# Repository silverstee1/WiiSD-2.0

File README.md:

# WiiSD-2.0
WiiSD 2.0 Upgrade PCB

Replacement upgrade PCB for WiiSD adapters sold on aliexpress/amazon etc to V2.0 for use on GameCube's Front Memcard Slot B

Based on the SD2SP2 2.0 made by Extrems, Thank you for your hard work!

**Important**

When using the adapter make sure to have the Latest Version of Swiss, Due to the way Swiss handles it in SLOT A it 
acts like a normal speed Passive SDGecko, in SLOT B it works in Semi-Passive 2.0 enhanced speed mode.

https://github.com/emukidid/swiss-gc

WiiSD 2.0 BOM
=====================================
The PCB must be ordered (e.g. from jlcpcb) in 0.8mm thickness with surface finish ENIG at minimum.

**WiiSD V2.0 PCB**

**J2:** SD Slot - Digikey Part# 2223-SD-4-BCT-ND

LCSC Part# C7529393

alt LCSC Part# C266601 , C961674

**U1:** OR Gate IC - DigiKey Part# 296-1093-1-ND

LCSC Part# C7470

Alt Nexperia Digikey Part# 1727-3067-1-ND

LCSC Alt Nexperia Part# C12488

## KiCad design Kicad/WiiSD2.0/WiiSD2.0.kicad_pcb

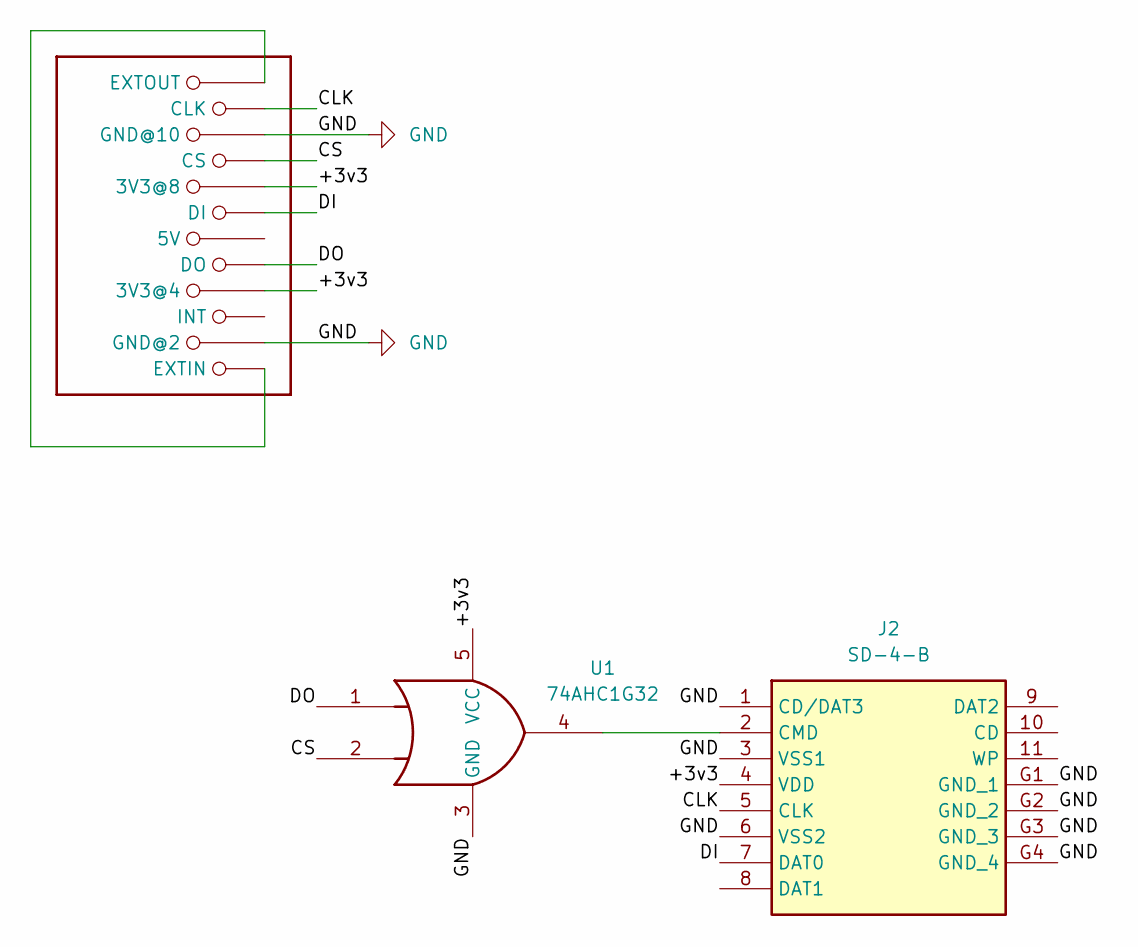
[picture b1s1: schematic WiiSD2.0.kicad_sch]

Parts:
J1: GC_MEMCARD
J2: SD-4-B; SD4B; Manufacturer_Part_Number SD-4-B
U1: 74AHC1G32; SC-74A-5_1.55x2.9mm_P0.95mm

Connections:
/+3v3: J1.4 (3V3@4), J1.8 (3V3@8), J2.4 (VDD), U1.5 (VCC)
/CLK: J1.11 (CLK), J2.5 (CLK)
/CS: J1.9 (CS), U1.2
/DI: J1.7 (DI), J2.7 (DAT0)
/DO: J1.5 (DO), U1.1
GND: J1.2 (GND@2), J1.10 (GND@10), J2.1 (CD/DAT3), J2.3 (VSS1), J2.6 (VSS2), J2.G1 (GND_1), J2.G2 (GND_2), J2.G3 (GND_3), J2.G4 (GND_4), U1.3 (GND)
unnamed: J1.1 (EXTIN), J1.12 (EXTOUT)
unnamed: J2.2 (CMD), U1.4

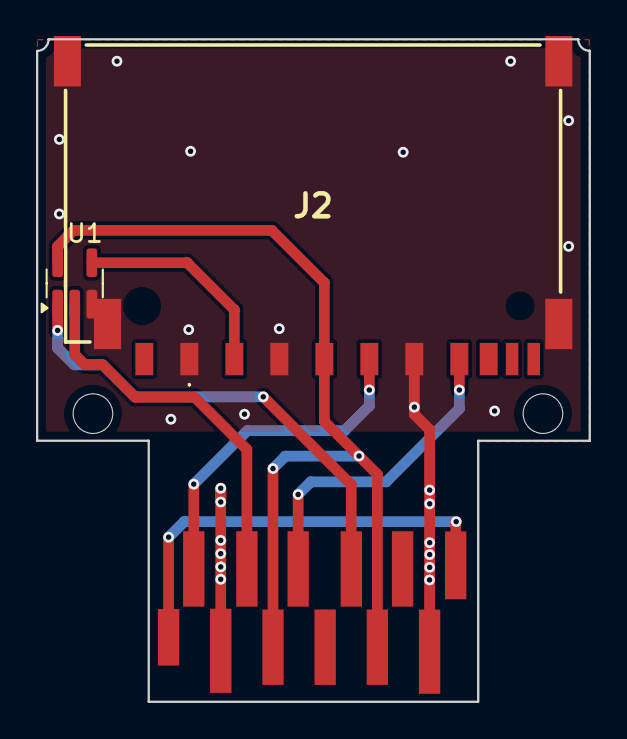
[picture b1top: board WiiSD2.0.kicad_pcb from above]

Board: 2 copper layers, 30.7 x 36.8 mm, 3 parts (0 on the bottom side), 8 nets.

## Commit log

2024-10-04 project upload
    upload pcb gerbers and project files
